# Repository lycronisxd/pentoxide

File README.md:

<h1 align="center">
  <picture>
  <source media="(prefers-color-scheme: dark)" srcset="https://github.com/user-attachments/assets/7219ccd8-d57b-41d6-96ce-b18b46f74935">
  <source media="(prefers-color-scheme: light)" srcset="https://github.com/user-attachments/assets/e426a1b6-aba4-4cd7-84bb-a8587f43f761">
  
  </picture>
</h1>

<h3 align="center">
  <picture>
  <source media="(prefers-color-scheme: dark)" srcset="https://github.com/user-attachments/assets/bf6074c8-e379-4ea4-a1d4-aef35d5d1d9c">
  <source media="(prefers-color-scheme: light)" srcset="https://github.com/user-attachments/assets/225eb73b-afd0-433c-afb1-c990a066f6d8">
  
  </picture>
  <div align="center">

  </div>
</h3>

<hr>

<!-- main body -->

<h3 align="center">
  <picture>
  <source media="(prefers-color-scheme: dark)" srcset="https://github.com/user-attachments/assets/0eb199f3-a66a-426e-8b88-3ce38c6fcc99">
  <source media="(prefers-color-scheme: light)" srcset="https://github.com/user-attachments/assets/3255cb05-ad44-49c5-b112-34e3b81043f4">
  
  </picture>
  <pre align="left">
pentoxide is an 18-key macro pad designed for creators and developers,
blending design language and function.
<br \>
built on top of QMK firmware with VIA compatibility,
pentoxide supports per-key rgb and a 128x160 1.8 inch lcd.
</pre>
</h3>

<hr>

<h3 align="center">
  <picture>
  <source media="(prefers-color-scheme: dark)" srcset="https://github.com/user-attachments/assets/8696bc60-909f-4c6e-ad67-8837299f265d">
  <source media="(prefers-color-scheme: light)" srcset="https://github.com/user-attachments/assets/cbb11c29-4aa7-4d3f-bdc8-6d2b004aac17">
  
  </picture>
<pre align="left">
{
"microcontroller": "raspberry-pi-rp2040",
"cpu-cores": "dual-core",
"clock-speed": "133-mhz",
"on-board-memory": "264-kb",
"gpio-pins": "30x",
"main-pcb": "pentoxide-mainboard",
"1u-mx-switches": "18x",
"switch-type": "everglide-aqua-king",
"rgb-capability": "y",
"rgb-leds": "18x",
"hotswap-capability": "y",
"kailh-hotswap-sockets": "18x",
"communication-sockets": "22x",
"display-size": "1.8-inch",
"display-resolution": "128x160",
"display-type": "tft-lcd",
"display-controller": "st7735s",
"firmware": "qmk",
"via-compatibility": "y"
}
</pre>
</h3>

<hr>

<h3 align="center">
  <picture>
  <source media="(prefers-color-scheme: dark)" srcset="https://github.com/user-attachments/assets/8fcd9fb2-011e-4284-a5a9-fb2776e90f1c">
  <source media="(prefers-color-scheme: light)" srcset="https://github.com/user-attachments/assets/7539e3ad-ad35-4bb8-8679-a545f65c9159">
  
  </picture>
  <br \>
  <br \>
  <br \>
  <br \>
  <br \>
  <br \>

</h3>

<hr>

<h3 align="center">
  <picture>
    <source media="(prefers-color-scheme: dark)" srcset="https://github.com/user-attachments/assets/2efd42f7-1078-4c4d-a306-e1f4fbedd322">
    <source media="(prefers-color-scheme: light)" srcset="https://github.com/user-attachments/assets/5ac018fb-4700-4111-8b4f-f1ed9c2d6f2b">
    
  </picture>
<pre align="left">
link to the public onshape project.
<a href="https://cad.onshape.com/documents/c17d4654dfdc64fa37b92d7c/w/b8eaedabc024b5a89ea703d7/e/db311653fe3b2444e14a3d99">https://pentoxide.onshape.com</a>
link to repo kicad files.
<a href="https://github.com/lycronisxd/pentoxide/tree/main/pcb">cd /root/pentoxide/pcb</a>
link to repo 3d printing files.
<a href="https://github.com/lycronisxd/pentoxide/tree/main/3dprinting">cd /root/pentoxide/3dprinting</a>
link to thingiverse 3d printing files.
<a href="https://www.thingiverse.com/thing:7385880">https://www.pentoxide.thingiverse.com</a>
</pre>
</h3>

<hr>

<h3 align="center">
  <picture>
  <source media="(prefers-color-scheme: dark)" srcset="https://github.com/user-attachments/assets/4b0244e2-1685-40e0-b2d2-98d43885c8d7">
  <source media="(prefers-color-scheme: light)" srcset="https://github.com/user-attachments/assets/0805ec88-f31b-448b-9def-bbe6aa447988">
  
  </picture>
  <pre align="left">
&lt!DOCTYPE html&gt
  &lthtml lang="en"&gt
    &lthead&gt
      &ltmeta charset="UTF-8"&gt
      &lttitle&gtrelevant links!&lt/title&gt
    &lt/head&gt
  &ltbody&gt
      &lth1&gthey there! below are some links to other projects that you can follow!&lt/h1&gt
      &lthr&gt
      &ltp&gt&lta href="https://github.com/lycronisxd/a-shift"&gt<a href="https://github.com/lycronisxd/a-shift">a-shift</a>&lt/a&gt&lt/p&gt
      &ltp&gt&lta href="https://github.com/lycronisxd/oxide-one"&gt<a href="https://github.com/lycronisxd/oxide-one">oxide-one</a>&lt/a&gt&lt/p&gt
      &ltp&gt&lta href="https://github.com/lycronisxd/ohm"&gt<a href="https://github.com/lycronisxd/ohm">ohm</a>&lt/a&gt&lt/p&gt
      &ltp&gt&lta href="https://github.com/lycronisxd/peroxide"&gt<a href="https://github.com/lycronisxd/peroxide">peroxide</a>&lt/a&gt&lt/p&gt
      &ltp&gt&lta href="https://github.com/lycronisxd/polylactic"&gt<a href="https://github.com/lycronisxd/polylactic">polylactic</a>&lt/a&gt&lt/p&gt
  &lt/body&gt
  &lt!--
  @@@@@@@@@@@@@@@@@@@@@@@@@@@@@@@@@@@@@@@@@@@@@@%#*************************************************#@@
  @@@@@@@@@@@@@@@@@@@@@@@@@@@@@@@@@@@@@@@@@%#%@@=.                    ..*#+         +#*.           =%@
  @@@@@@@@@@@@@@@@@@@@@@@@@@@@@@@@@@@@@@@@%+.=%@=.                    ..--:         *@%.           =%@
  @@@@@#-=+-:::-%@@@@#-:::-*@@@=:#=:::-*@#-...:+=.:+#%%#*-..-*#=. .+##..*#+  .+#%%#*#@%. .:*#%%#=..=%@
  @@@@@*..-#%%+:.+@@-.=%%%=.=%@-..*%%*.:*@#=.=#%=+%@-:.-*@*:.:#@#-#@*...#@* -#@*-::+@@%..+@#:.:+%#:=%@
  @@@@@*.:#@@@@+..%*..====-:.*@-.+@@@%:.+@%+.=%@*%@-   .:%%=  .+%@@:. ..#@*.=@#:.  .*@%.-@%#****%@==%@
  @@@@#-%%-   .+%%.+@%.........#@+.  .%%+ .+@*. =..*@@@@#:.+@@%-...:@@@%:.=@+ -#@@@@= :@#.:#@@@@@@@@@@
  @@@@#-%@%-..+%@+..%@#...+@%-.#@+.  .%%+ .+@#:.++..#@@#-.-%@*:.*@=..#@%:.=@%-.-#%%=. :@%=.-%@@*::#@@@
  @@@@#-%%**%%%*:.  .-#%%%#=. .*#=.  .##+ .:*%%**%%+::::-#@@+:-#@@@#::+%=:+@@@*-:::+*:-@@@#=::::*%@@@@
  @@@@#-%%-                                     +%@@@@@@@@@@@@@@@@@@@@@@@@@@@@@@@@@@@@@@@@@@@@@@@@@@@@
  @@@@#-**-                                     +%@@@@@@@@@@@@@@@@@@@@@@@@@@@@@@@@@@@@@@@@@@@@@@@@@@@@
  @@@@@%%%%%%%%%%%%%%%%%%%%%%%%%%%%%%%%%%%%%%%%%@@@@@@@@@@@@@@@@@@@@@@@@@@@@@@@@@@@@@@@@@@@@@@@@@@@@@@
  --&gt
</pre>
</h3>
  
<hr>

<h3 align="center">

  <picture>
  <source media="(prefers-color-scheme: dark)" srcset="https://github.com/user-attachments/assets/031f2031-ec8b-4581-bf83-9b06f5faa409">
  <source media="(prefers-color-scheme: light)" srcset="https://github.com/user-attachments/assets/4cdb615e-4db5-4dbc-abcc-0074ae9797d5">
  
  </picture>
</h3>

| item no. | part no. | part name          | qty. | supplier   | unit cost | total cost | notes                                  |
|----------|----------|--------------------|----:|------------|----------:|-----------:|----------------------------------------|
| 1 | PCB-001 | pentoxide-pcb | 1 | jlcpcb | $11.90 | $11.90 | - |
| 2 | PCB-002 | 0805-100nf-cap | 18 | aliexpress | $0.04 | $3.62 | 100 pcs was the smallest i could find. |
| 3 | PCB-003 | 0805-330-res | 1 | aliexpress | $2.64 | $2.64 | - |
| 4 | PCB-004 | sod-123-1n4148w | 18 | aliexpress | $0.02 | $1.53 | 100 pcs was the smallest i could find. |
| 5 | PCB-005 | kailh-hs-socket | 18 | aliexpress | $0.22 | $6.66 | 30 pcs was the smallest i could find. |
| 6 | PCB-006 | sk6812-mini-e-led | 18 | aliexpress | $0.08 | $4.09 | 50 pcs was the smallest i could find. |
| 7 | PCB-007 | 128x160-lcd | 1 | aliexpress | $3.82 | $3.82 | - |
| 8 | PCB-008 | rp2040-pro-micro | 1 | aliexpress | $3.79 | $3.79 | - |
| 9 | SW-001 | mmd-aqua-king | 18 | aliexpress | $0.53 | $15.81 | 30 pcs was the smallest i could find. |
| 10 | SW-002 | cherry-keycap | 18 | aliexpress | $0.30 | $5.91 | 20 pcs was the smallest i could find. |
| 11 | MNT-001 | m4-bolt | 10 | aliexpress | $8.97 | $8.97 | see notes below. |
| 12 | MNT-002 | m2-bolt | 4 | aliexpress | - | - | price included in M4 bolt price. |
| 13 | MNT-003 | m2-nut | 4 | aliexpress | - | - | price included in M4 bolt price. |
| 14 | MNT-004 | m4-insert | 10 | aliexpress | $0.04 | $4.02 | 100 pcs was the smallest i could find. |
| 15 | 3D-001 | pentoxide-plate | 1 | N/A | - | - | custom print / print legion. |
| 16 | 3D-002 | pentoxide-case | 1 | N/A | - | - | custom print / print legion. |

<br />
<b>total cost : 72.76 USD (54.24 GBP)</b>
<hr>

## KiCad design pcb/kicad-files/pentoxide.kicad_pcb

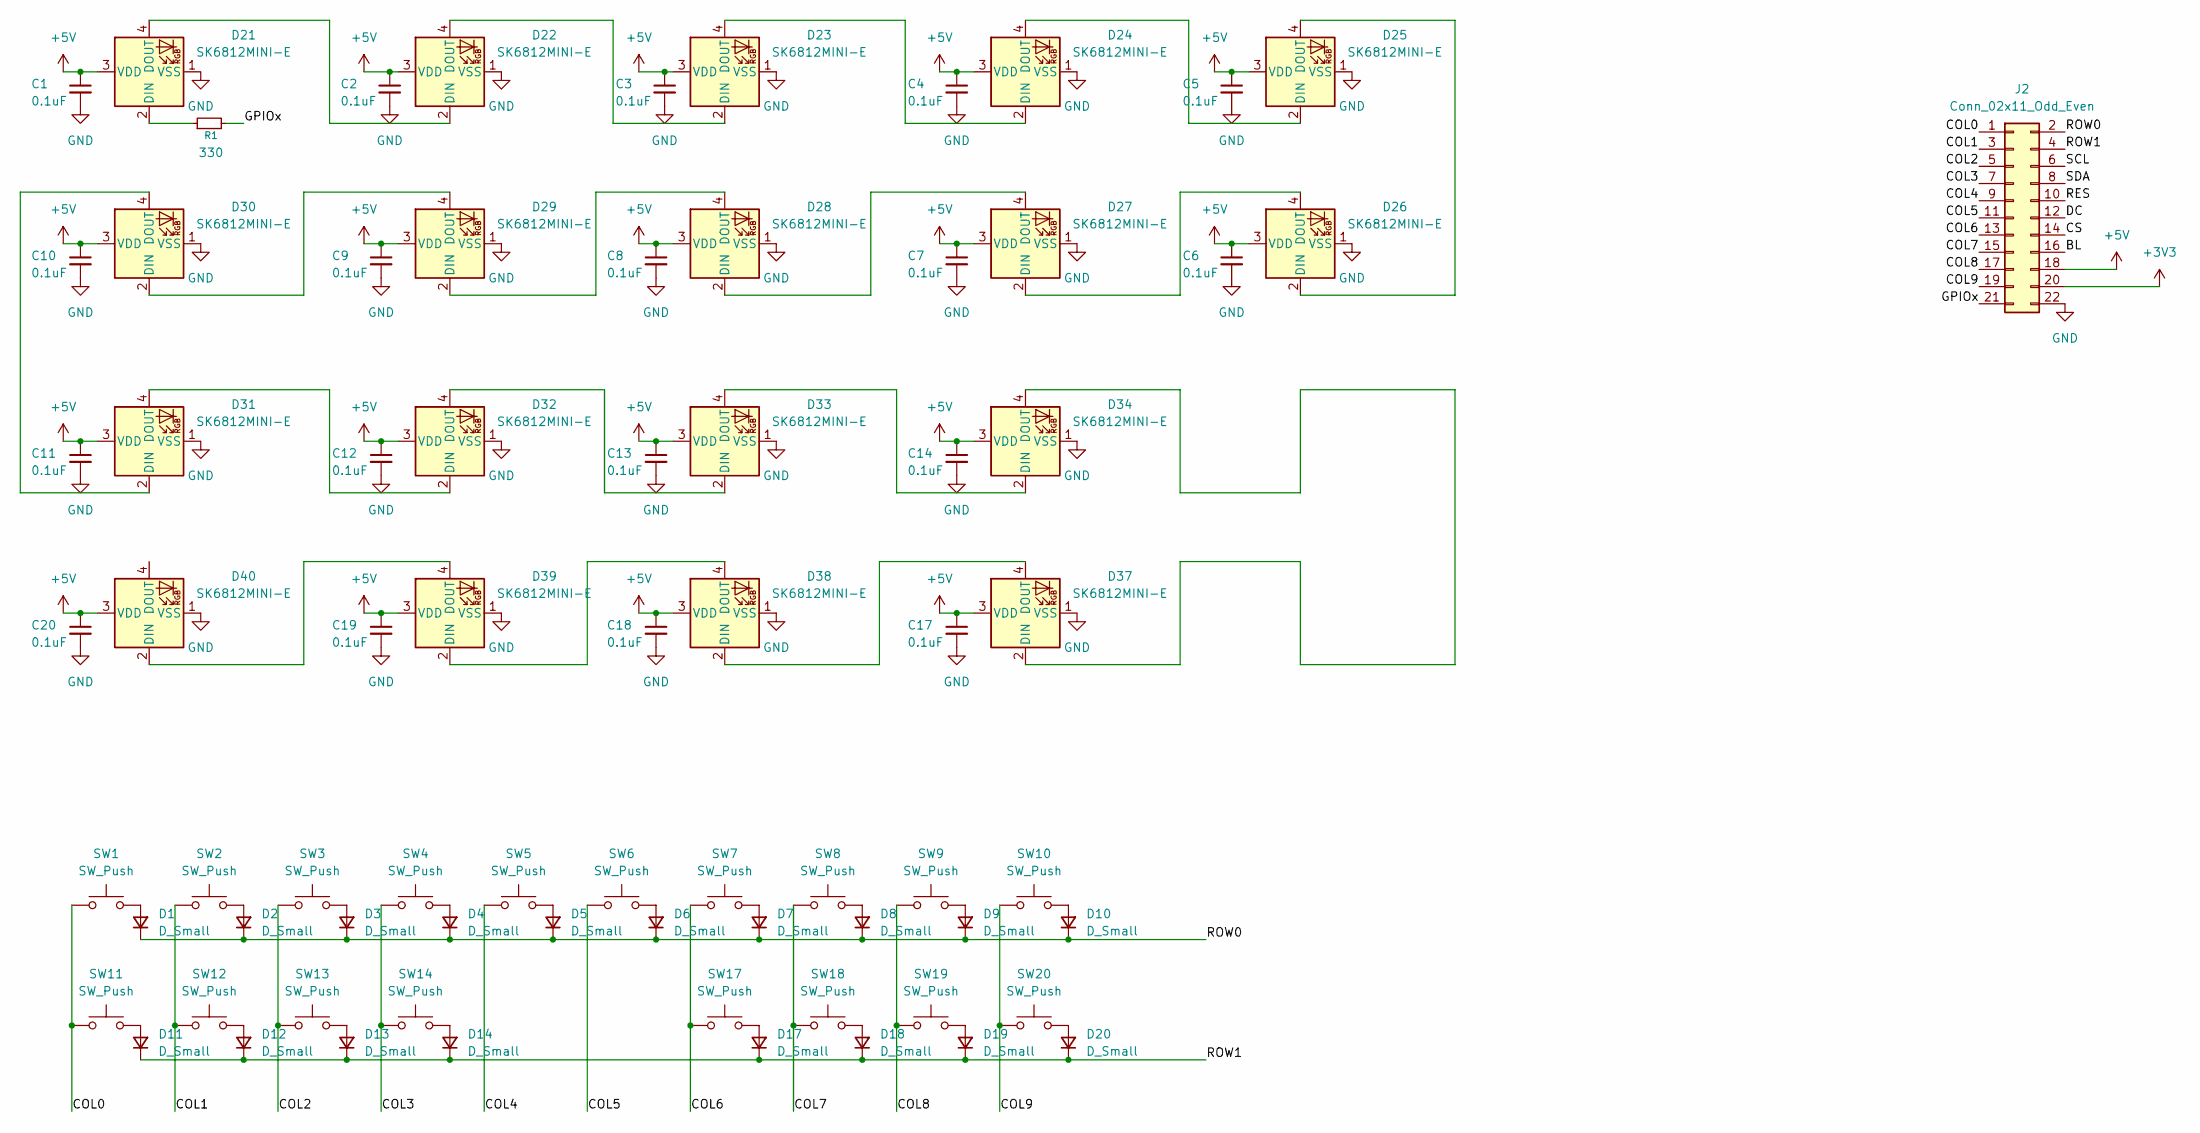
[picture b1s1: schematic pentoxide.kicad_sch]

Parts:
C1, C2, C3, C4, C5, C6, C7, C8, C9, C10, C11, C12, C13, C14, C17, C18, C19, C20: 0.1uF; C_0805_2012Metric_Pad1.18x1.45mm_HandSolder
D1, D2, D3, D4, D5, D6, D7, D8, D9, D10, D11, D12, D13, D14, D17, D18, D19, D20: D_Small; D_SOD-123
D21, D22, D23, D24, D25, D26, D27, D28, D29, D30, D31, D32, D33, D34, D37, D38, D39, D40: SK6812MINI-E; LED_SK6812MINI-E_3.2x2.8mm_P1.5mm_ReverseMount
J2: Conn_02x11_Odd_Even; PinHeader_2x11_P2.54mm_Vertical
R1: 330; R_0805_2012Metric_Pad1.20x1.40mm_HandSolder
SW1, SW2, SW3, SW4, SW5, SW6, SW7, SW8, SW9, SW10, SW11, SW12, SW13, SW14, SW17, SW18, SW19, SW20: SW_Push; MX-Hotswap-1U

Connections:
+3V3: J2.20
+5V: C1.1, C2.1, C3.1, C4.1, C5.1, C6.1, C7.1, C8.1, C9.1, C10.1, C11.1, C12.1, C13.1, C14.1, C17.1, C18.1, C19.1, C20.1, D21.3 (VDD), D22.3 (VDD), D23.3 (VDD), D24.3 (VDD), D25.3 (VDD), D26.3 (VDD), D27.3 (VDD), D28.3 (VDD), D29.3 (VDD), D30.3 (VDD), D31.3 (VDD), D32.3 (VDD), D33.3 (VDD), D34.3 (VDD), D37.3 (VDD), D38.3 (VDD), D39.3 (VDD), D40.3 (VDD), J2.18
/BL: J2.16
/COL0: J2.1, SW1.1, SW11.1
/COL1: J2.3, SW2.1, SW12.1
/COL2: J2.5, SW3.1, SW13.1
/COL3: J2.7, SW4.1, SW14.1
/COL4: J2.9, SW5.1
/COL5: J2.11, SW6.1
/COL6: J2.13, SW7.1, SW17.1
/COL7: J2.15, SW8.1, SW18.1
/COL8: J2.17, SW9.1, SW19.1
/COL9: J2.19, SW10.1, SW20.1
/CS: J2.14
/DC: J2.12
/GPIOx: J2.21, R1.2
/RES: J2.10
/ROW0: D1.1 (K), D2.1 (K), D3.1 (K), D4.1 (K), D5.1 (K), D6.1 (K), D7.1 (K), D8.1 (K), D9.1 (K), D10.1 (K), J2.2
/ROW1: D11.1 (K), D12.1 (K), D13.1 (K), D14.1 (K), D17.1 (K), D18.1 (K), D19.1 (K), D20.1 (K), J2.4
/SCL: J2.6
/SDA: J2.8
GND: C1.2, C2.2, C3.2, C4.2, C5.2, C6.2, C7.2, C8.2, C9.2, C10.2, C11.2, C12.2, C13.2, C14.2, C17.2, C18.2, C19.2, C20.2, D21.1 (VSS), D22.1 (VSS), D23.1 (VSS), D24.1 (VSS), D25.1 (VSS), D26.1 (VSS), D27.1 (VSS), D28.1 (VSS), D29.1 (VSS), D30.1 (VSS), D31.1 (VSS), D32.1 (VSS), D33.1 (VSS), D34.1 (VSS), D37.1 (VSS), D38.1 (VSS), D39.1 (VSS), D40.1 (VSS), J2.22
unnamed: D1.2 (A), SW1.2
unnamed: D2.2 (A), SW2.2
unnamed: D3.2 (A), SW3.2
unnamed: D4.2 (A), SW4.2
unnamed: D5.2 (A), SW5.2
unnamed: D6.2 (A), SW6.2
unnamed: D7.2 (A), SW7.2
unnamed: D8.2 (A), SW8.2
unnamed: D9.2 (A), SW9.2
unnamed: D10.2 (A), SW10.2
unnamed: D11.2 (A), SW11.2
unnamed: D12.2 (A), SW12.2
unnamed: D13.2 (A), SW13.2
unnamed: D14.2 (A), SW14.2
unnamed: D17.2 (A), SW17.2
unnamed: D18.2 (A), SW18.2
unnamed: D19.2 (A), SW19.2
unnamed: D20.2 (A), SW20.2
unnamed: D21.2 (DIN), R1.1
unnamed: D21.4 (DOUT), D22.2 (DIN)
unnamed: D22.4 (DOUT), D23.2 (DIN)
unnamed: D23.4 (DOUT), D24.2 (DIN)
unnamed: D24.4 (DOUT), D25.2 (DIN)
unnamed: D25.4 (DOUT), D26.2 (DIN)
unnamed: D26.4 (DOUT), D27.2 (DIN)
unnamed: D27.4 (DOUT), D28.2 (DIN)
unnamed: D28.4 (DOUT), D29.2 (DIN)
unnamed: D29.4 (DOUT), D30.2 (DIN)
unnamed: D30.4 (DOUT), D31.2 (DIN)
unnamed: D31.4 (DOUT), D32.2 (DIN)
unnamed: D32.4 (DOUT), D33.2 (DIN)
unnamed: D33.4 (DOUT), D34.2 (DIN)
unnamed: D34.4 (DOUT), D37.2 (DIN)
unnamed: D37.4 (DOUT), D38.2 (DIN)
unnamed: D38.4 (DOUT), D39.2 (DIN)
unnamed: D39.4 (DOUT), D40.2 (DIN)

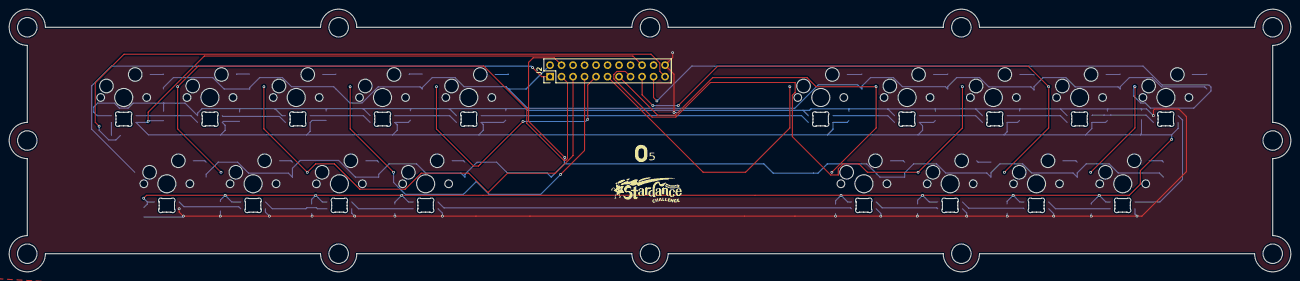
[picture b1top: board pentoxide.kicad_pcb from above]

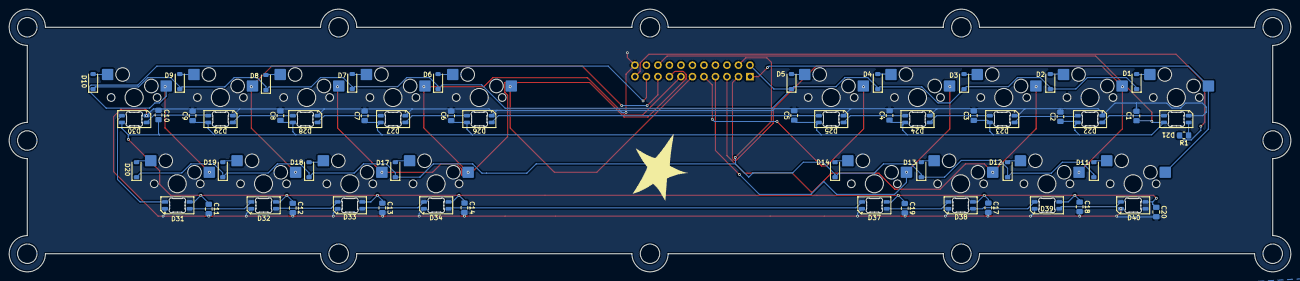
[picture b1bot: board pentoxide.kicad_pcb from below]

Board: 2 copper layers, 283.0 x 58.0 mm, 74 parts (55 on the bottom side), 51 nets.

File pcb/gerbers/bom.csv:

Designator,Footprint,Quantity,Value,LCSC Part #
"C1, C10, C11, C12, C13, C14, C17, C18, C19, C2, C20, C3, C4, C5, C6, C7, C8, C9",805,18,0.1uF,C14663
"D1, D10, D11, D12, D13, D14, D17, D18, D19, D2, D20, D3, D4, D5, D6, D7, D8, D9",D_SOD-123,18,D_Small,C241939
"D21, D22, D23, D24, D25, D26, D27, D28, D29, D30, D31, D32, D33, D34, D37, D38, D39, D40",LED_SK6812MINI-E_3.2x2.8mm_P1.5mm_ReverseMount,18,SK6812MINI-E,C5149201
J2,PinHeader_2x11_P2.54mm_Vertical,1,DNP,
R1,805,1,330,C2907002
"SW1, SW10, SW11, SW12, SW13, SW14, SW17, SW18, SW19, SW2, SW20, SW3, SW4, SW5, SW6, SW7, SW8, SW9",MX-Hotswap-1U,18,SW_Push,C49352235
